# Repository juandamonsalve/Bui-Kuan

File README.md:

# Bui-Kuan
El proyecto "Bui-Kuan" busca mejorar la atención médica en Sora, Colombia. Enfrentando desafíos como la falta de acceso a servicios médicos de calidad, sobresaturación hospitalaria y barreras geográficas, el prototipo se centra en sistemas embebidos, incorporando sensores de temperatura, frecuencia cardíaca y saturación de oxígeno.

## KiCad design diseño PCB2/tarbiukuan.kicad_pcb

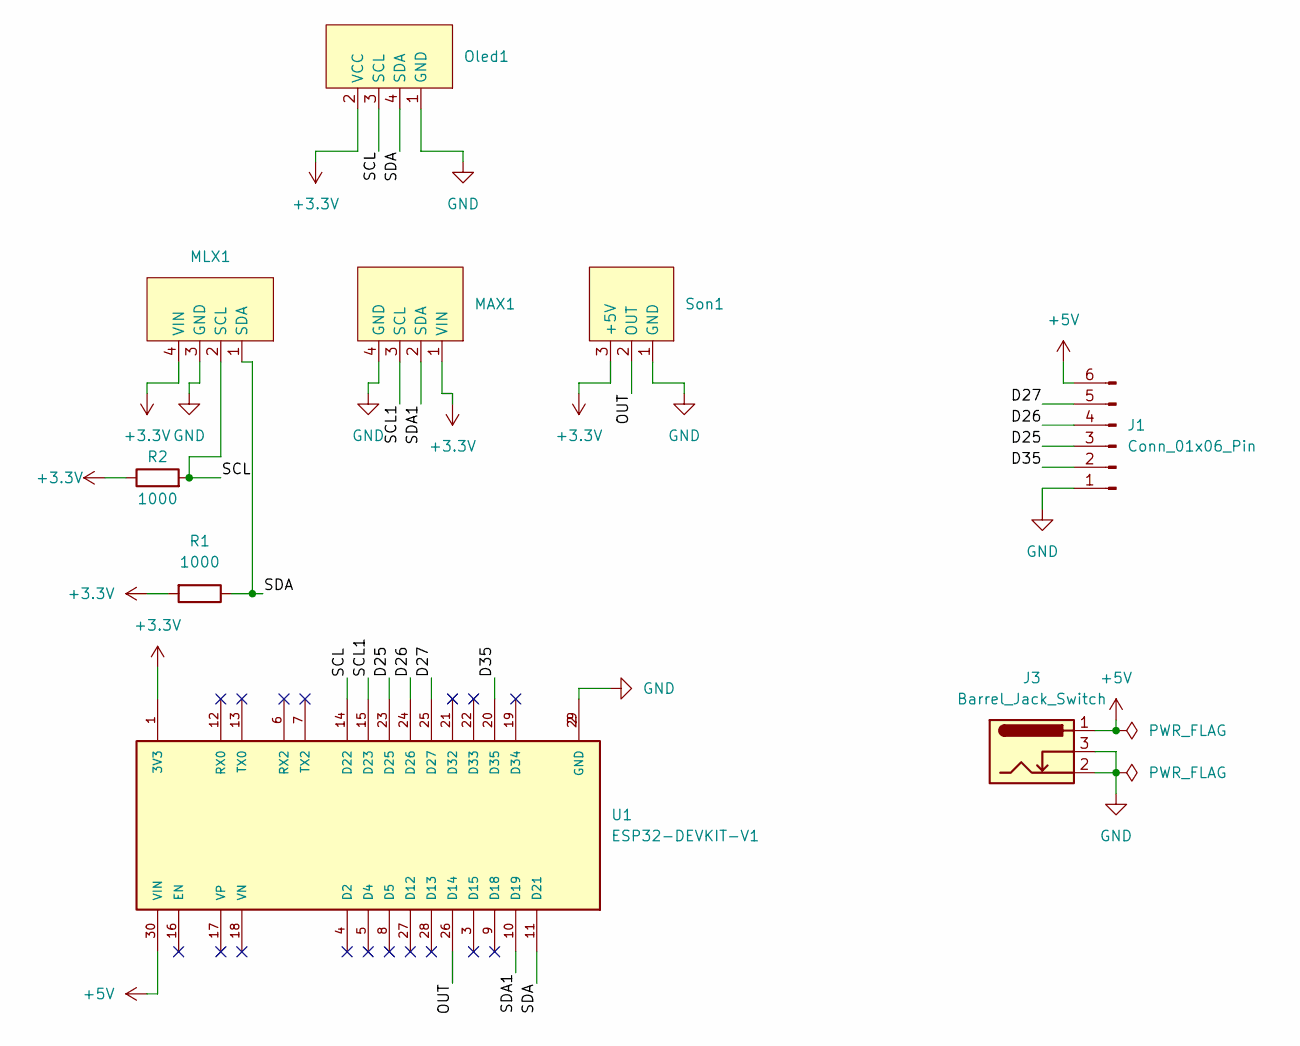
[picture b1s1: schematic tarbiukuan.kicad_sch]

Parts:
J1: Conn_01x06_Pin; PinHeader_1x06_P2.54mm_Vertical
J3: Barrel_Jack_Switch; BarrelJack_Horizontal
MAX1: max30102
MLX1: temperatura
Oled1: Pantallaoled
R1: 1000; R_Axial_DIN0207_L6.3mm_D2.5mm_P7.62mm_Horizontal
R2: 1000; R_Axial_DIN0204_L3.6mm_D1.6mm_P5.08mm_Horizontal
Son1: sonido
U1: ESP32-DEVKIT-V1; MODULE_ESP32_DEVKIT_V1; PARTREV N/A

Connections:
+3.3V: MAX1.1 (VIN), MLX1.4 (VIN), Oled1.2 (VCC), R1.2, R2.1, Son1.3 (+5V), U1.1 (3V3)
+5V: J1.6, J3.1, U1.30 (VIN)
/D25: J1.3, U1.23 (D25)
/D26: J1.4, U1.24 (D26)
/D27: J1.5, U1.25 (D27)
/D35: J1.2, U1.20 (D35)
/OUT: Son1.2 (OUT), U1.26 (D14)
/SCL: MLX1.2 (SCL), Oled1.3 (SCL), R2.2, U1.14 (D22)
/SCL1: MAX1.3 (SCL), U1.15 (D23)
/SDA: MLX1.1 (SDA), Oled1.4 (SDA), R1.1, U1.11 (D21)
/SDA1: MAX1.2 (SDA), U1.10 (D19)
GND: J1.1, J3.2, J3.3, MAX1.4 (GND), MLX1.3 (GND), Oled1.1 (GND), Son1.1 (GND), U1.2 (GND), U1.29 (GND)

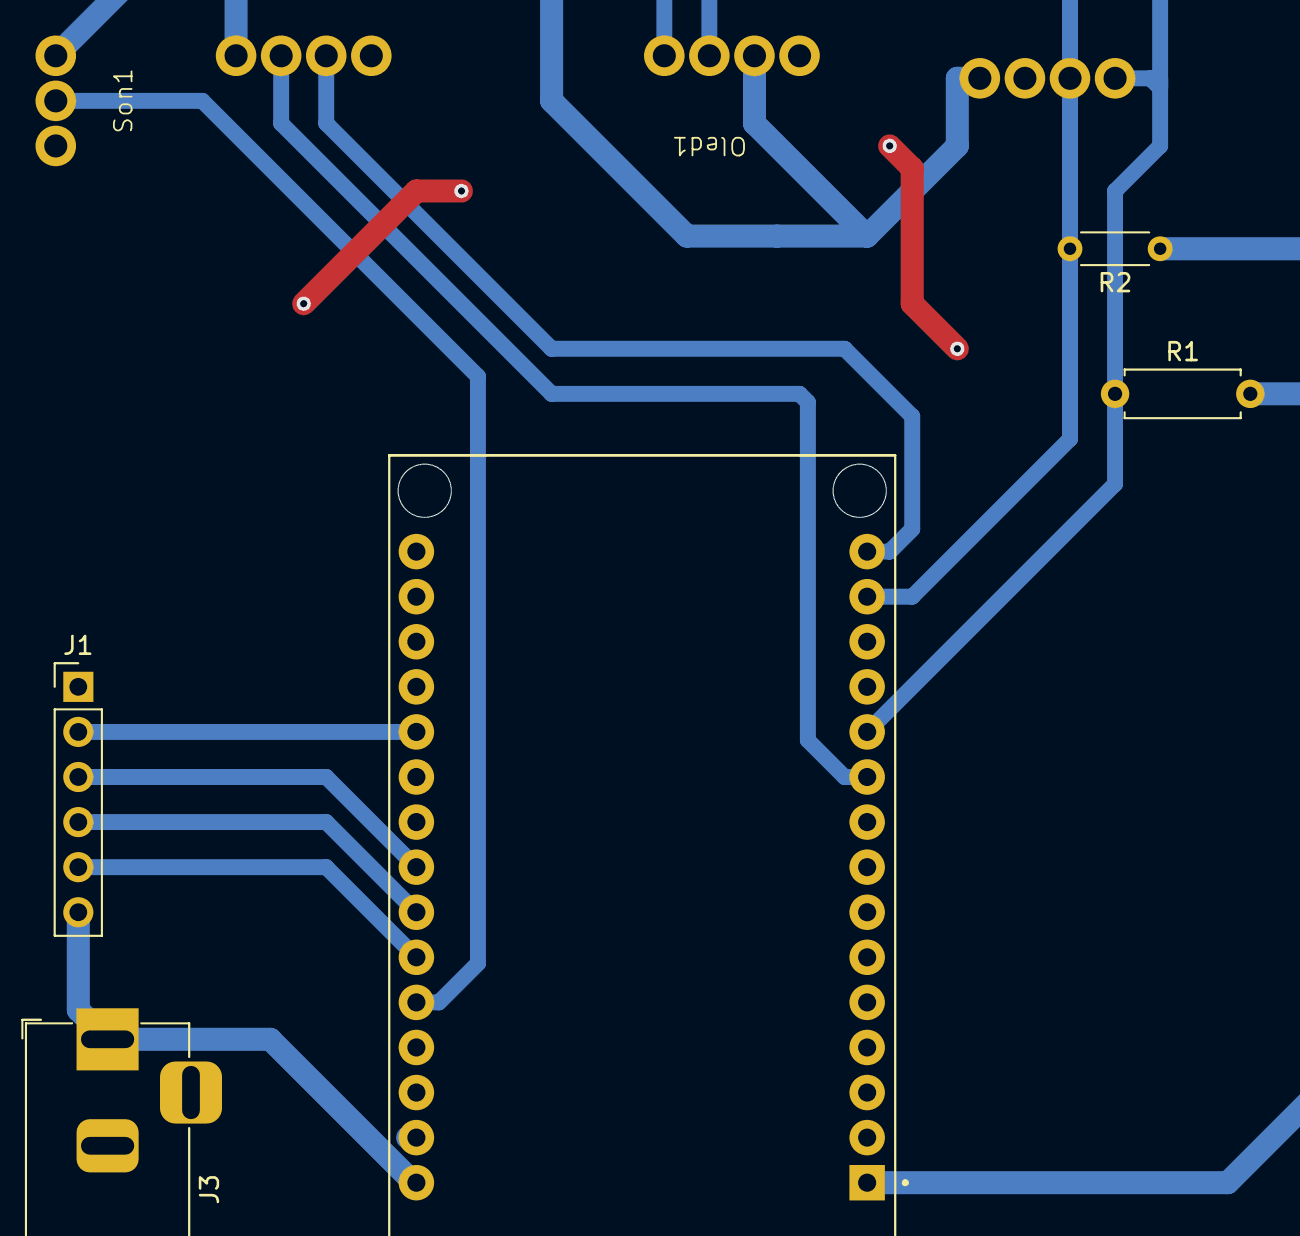
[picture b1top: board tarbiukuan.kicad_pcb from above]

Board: 2 copper layers, 9 parts (0 on the bottom side), 12 nets.

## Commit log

2023-11-29 Create circular_buffer
2023-11-29 frec
2023-11-29 Create freccar
2023-11-29 Create max30102
2023-11-29 Create mlx90614
2023-11-29 Create pulsometro
2023-11-29 Create sp02temp
2023-11-29 Create ssd1306
2023-11-29 inicio de 3d
2023-11-29 Diseño
2023-12-01 lo que faltaba
